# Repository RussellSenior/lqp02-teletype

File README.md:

This is a project motivated by a desire to create a daisywheel teletype, to give a
similar experience to that of a Model 33ASR teletype, but with upper and lowercase
characters. Thanks to Hugh Pyle and his fantastic [Twitch channel](https://www.twitch.tv/33asr) for the
inspiration.  Thanks also to Chris Gregg and his project:
https://github.com/tofergregg/IBM-Wheelwriter-Hack and to this very similar project
by Stephen Casner: https://github.com/IBM-1620/Junior.

The goal is to intercept user input from the keyboard and send it to a remote computer
and receive the echoed characters from the remote computer and send the corresponding
commands to the printing mechanism for hardcopy output.

I obtained an IBM Wheelwriter 5 from the Tektronix Surplus Store (open two days a month,
first and third Thursdays, from 2pm to 4pm) on the Beaverton Oregon campus of Tektronix.
This typewriter came with the PC Printer option, which hangs on the back of the case
and interfaces by a 6 (or 7?) pin bus. The cost of the typewriter was $25. I purchased
two new-in-box ribbon cartridges from the same location for $0.50 each.

In the process of working on the IBM Wheelwriter, I was given a couple of DEC LQP02 serial
daisywheel printers. This repository reflects the work on the LQP02.  These have some advantages,
including the availability of a native RS-232 interface and full ASCII character set wheels.

This project uses a Teensy 3.1 with a PS/2 keyboard, and two serial ports.  One serial port
talks to the printer and the other talks to a remote computer.  It decodes keyboard events using
the Ps2KeyboardHost library from Steve Benz: https://github.com/SteveBenz/PS2KeyboardHost,
sends them to the remote computer, reads data coming from the remote computer and sends them
to the printer's serial port.

The printer is constrained in the rate at which it can turn bytes into print, so flow control
is important. It turns out that the printer does XON/XOFF flow control, and the remote computer
does RTS/CTS hardware flow control, so the Teensy program looks for XON/XOFF from the printer
and stops reading from the computer serial port when it last saw XOFF, which lets the hardware
UART's flow control just work.

One of the disadvantages of the LQP02 is that it was intended as a strictly output device, and
as a result being able to see what you are typing is not prioritized.  I saw a video on youtube
(https://www.youtube.com/watch?v=TRxz4x45i54) which used the vertical motion control to roll
the platen to lift the active printing line up above the printing mechanism at appropriate
moments so that you can see what you have typed.  On the LQP02, 12 lines seems about right.
When rolling the paper back down to continue printing, I am rolling an extra line down and then
back up one to hopefully improve vertical registration.  Thanks Blake Thomas for the idea.

The other disadvantage is that the LQP02 prints bi-directionally, which means that it needs
to pause on input to see if more input is coming. If there is, then it can effectively read
ahead and see the opportunity to print backwards. This introduces an annoying lag between input
and when the characters are struck. So far, no means of turning off this delay has been found.

There are a bunch of TODO's:

 * Add a toggle switch to switch between Line and Local mode;
 * Support the mini-DIN8 connected Sun Keyboard;
 * Support output to an IBM Wheelwriter;

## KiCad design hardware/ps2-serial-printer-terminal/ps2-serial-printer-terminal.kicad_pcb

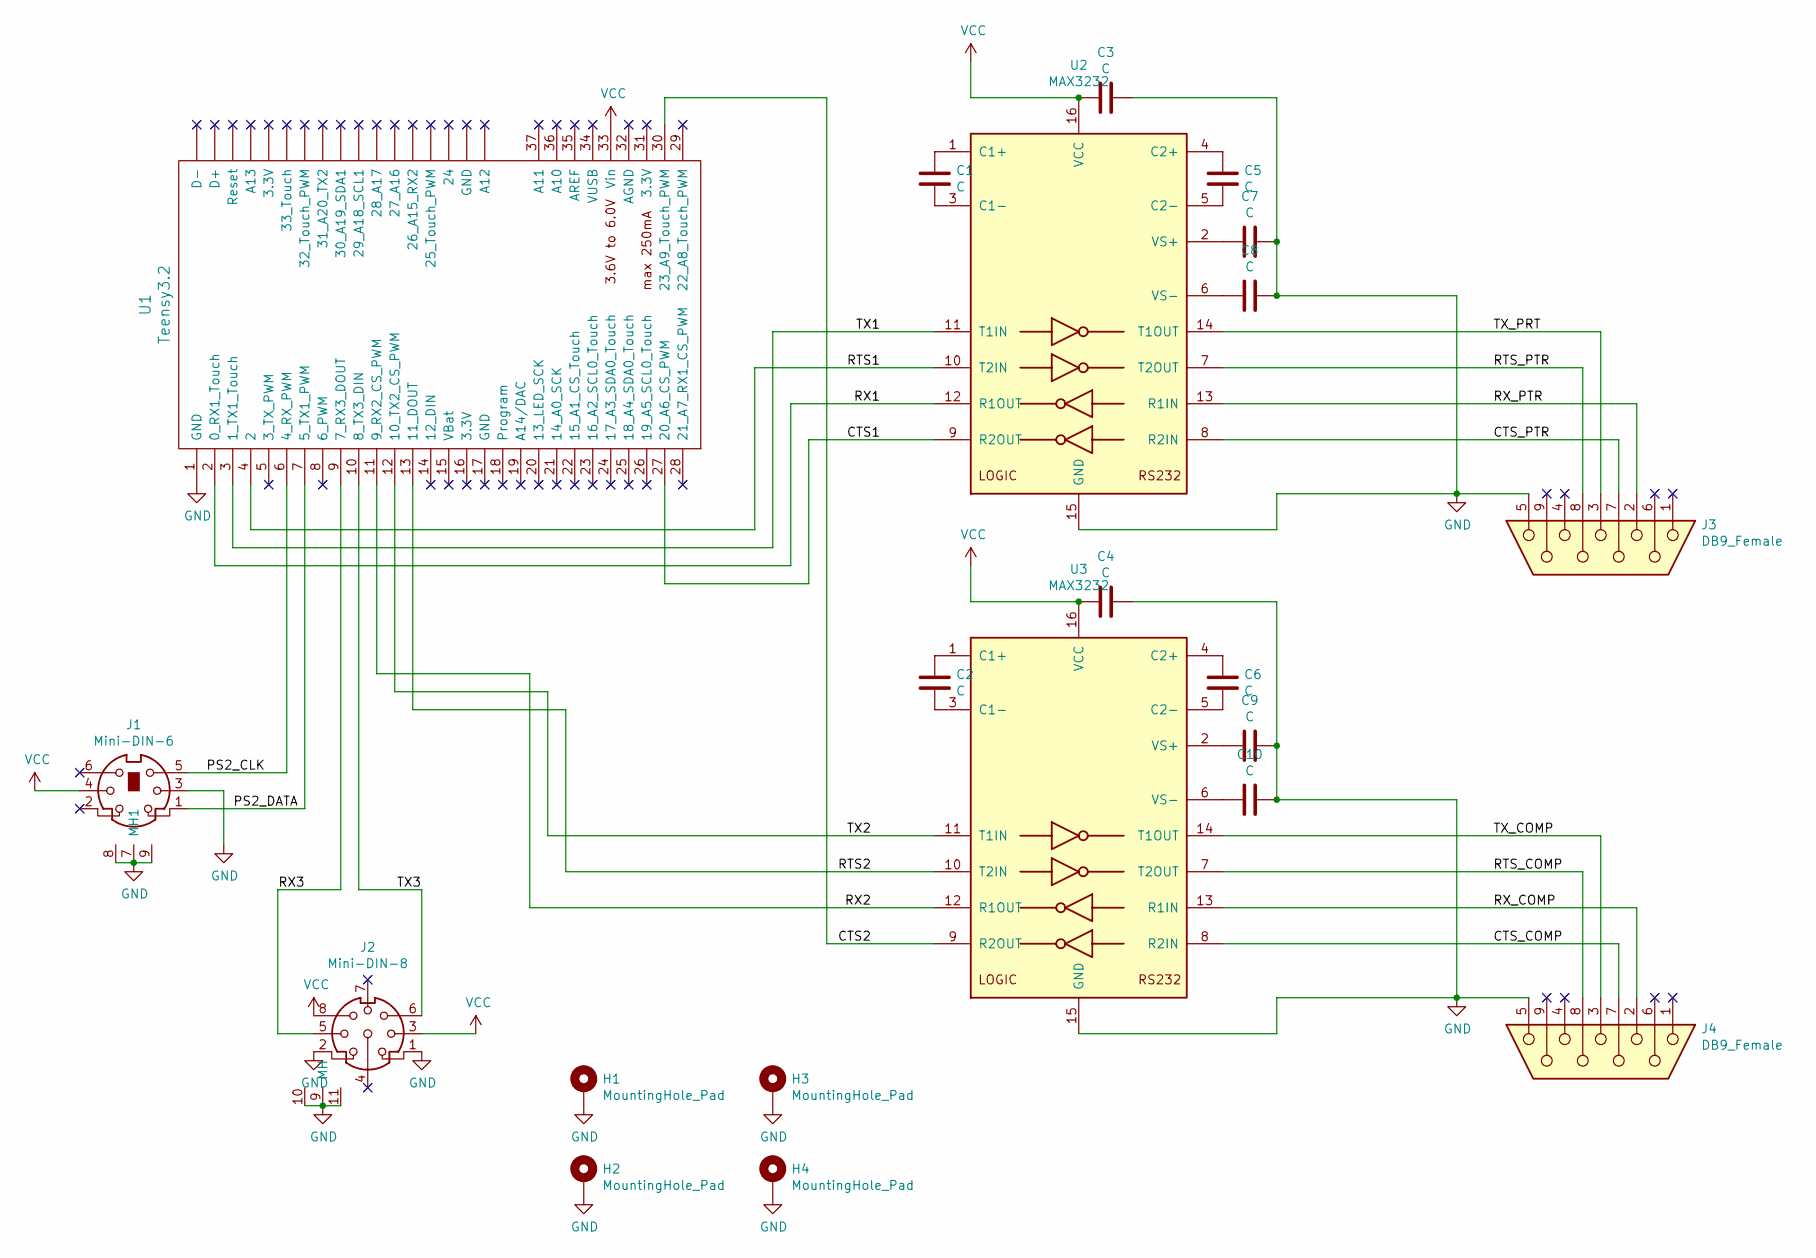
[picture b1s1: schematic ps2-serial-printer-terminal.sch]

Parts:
C1, C2, C3, C4, C5, C6, C7, C8, C9, C10: C; C_0805_2012Metric_Pad1.15x1.40mm_HandSolder
H1, H2, H3, H4: MountingHole_Pad; MountingHole_3mm_Pad_Via
J1: Mini-DIN-6; 5749231-1
J2: Mini-DIN-8; MD-80SM
J3, J4: DB9_Female; DSUB-9_Female_Horizontal_P2.77x2.84mm_EdgePinOffset14.56mm_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
U1: Teensy3.2; Teensy30_31_32_LC_minus
U2, U3: MAX3232; SOIC-16_3.9x9.9mm_P1.27mm

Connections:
/CTS1: U1.27 (20_A6_CS_PWM), U2.9 (R2OUT)
/CTS2: U1.30 (23_A9_Touch_PWM), U3.9 (R2OUT)
/CTS_COMP: J4.7, U3.8 (R2IN)
/CTS_PTR: J3.7, U2.8 (R2IN)
/PS2_CLK: J1.5, U1.6 (4_RX_PWM)
/PS2_DATA: J1.1, U1.7 (5_TX1_PWM)
/RTS1: U1.4 (2), U2.10 (T2IN)
/RTS2: U1.13 (11_DOUT), U3.10 (T2IN)
/RTS_COMP: J4.8, U3.7 (T2OUT)
/RTS_PTR: J3.8, U2.7 (T2OUT)
/RX1: U1.2 (0_RX1_Touch), U2.12 (R1OUT)
/RX2: U1.11 (9_RX2_CS_PWM), U3.12 (R1OUT)
/RX3: J2.5, U1.9 (7_RX3_DOUT)
/RX_COMP: J4.2, U3.13 (R1IN)
/RX_PTR: J3.2, U2.13 (R1IN)
/TX1: U1.3 (1_TX1_Touch), U2.11 (T1IN)
/TX2: U1.12 (10_TX2_CS_PWM), U3.11 (T1IN)
/TX3: J2.6, U1.10 (8_TX3_DIN)
/TX_COMP: J4.3, U3.14 (T1OUT)
/TX_PRT: J3.3, U2.14 (T1OUT)
GND: C3.1, C4.1, C7.1, C8.1, C9.1, C10.1, H1.1, H2.1, H3.1, H4.1, J1.3, J1.7 (MH1), J1.8, J1.9, J2.1, J2.2, J2.9 (MH), J2.10, J2.11, J3.5, J4.5, U1.1 (GND), U2.15 (GND), U3.15 (GND)
unnamed: C1.1, U2.1 (C1+)
unnamed: C1.2, U2.3 (C1-)
unnamed: C2.1, U3.1 (C1+)
unnamed: C2.2, U3.3 (C1-)
unnamed: C5.1, U2.4 (C2+)
unnamed: C5.2, U2.5 (C2-)
unnamed: C6.1, U3.4 (C2+)
unnamed: C6.2, U3.5 (C2-)
unnamed: C7.2, U2.2 (VS+)
unnamed: C8.2, U2.6 (VS-)
unnamed: C9.2, U3.2 (VS+)
unnamed: C10.2, U3.6 (VS-)
VCC: C3.2, C4.2, J1.4, J2.3, J2.8, U1.33 (Vin), U2.16 (VCC), U3.16 (VCC)

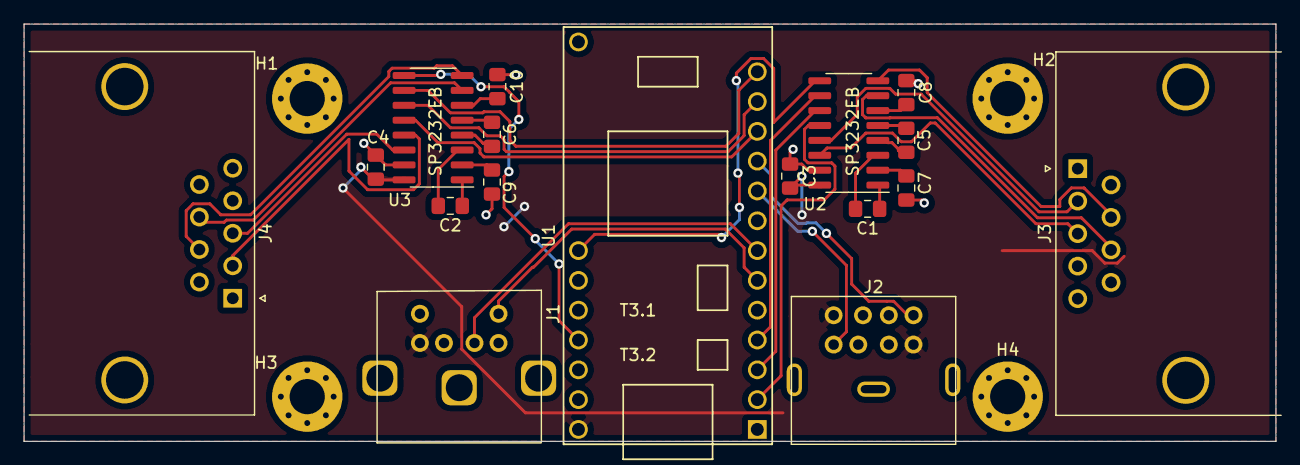
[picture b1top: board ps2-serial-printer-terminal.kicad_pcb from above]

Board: 2 copper layers, 106.7 x 35.6 mm, 21 parts (0 on the bottom side), 34 nets.

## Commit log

2019-05-12 first version with working flow control
2019-05-12 Add README.md
2019-05-18 add a form feed, line feed and reverse line feed to function keys
2019-05-18 add a feature to show text hidden by printing mechanism
    After 500ms of printing inactivity, roll platen up N lines (currently 8)
    to show state to user. Before printing again, roll platen back down N+1,
    then up one to return to the current location for new printing. This
    enhances the experience for the user, as they can see what they just typed
    or what the computer just typed back at them.
2019-06-19 it works, mostly!
2019-06-22 reflect some changes in the latest commit(s) in the README
2019-10-09 correct incorrect mapping of the right paren key
2020-04-29 remove trailing whitespace from README.md
2020-04-29 add another paragraph about annoyances
2020-06-22 render prototype circuit in kicad
